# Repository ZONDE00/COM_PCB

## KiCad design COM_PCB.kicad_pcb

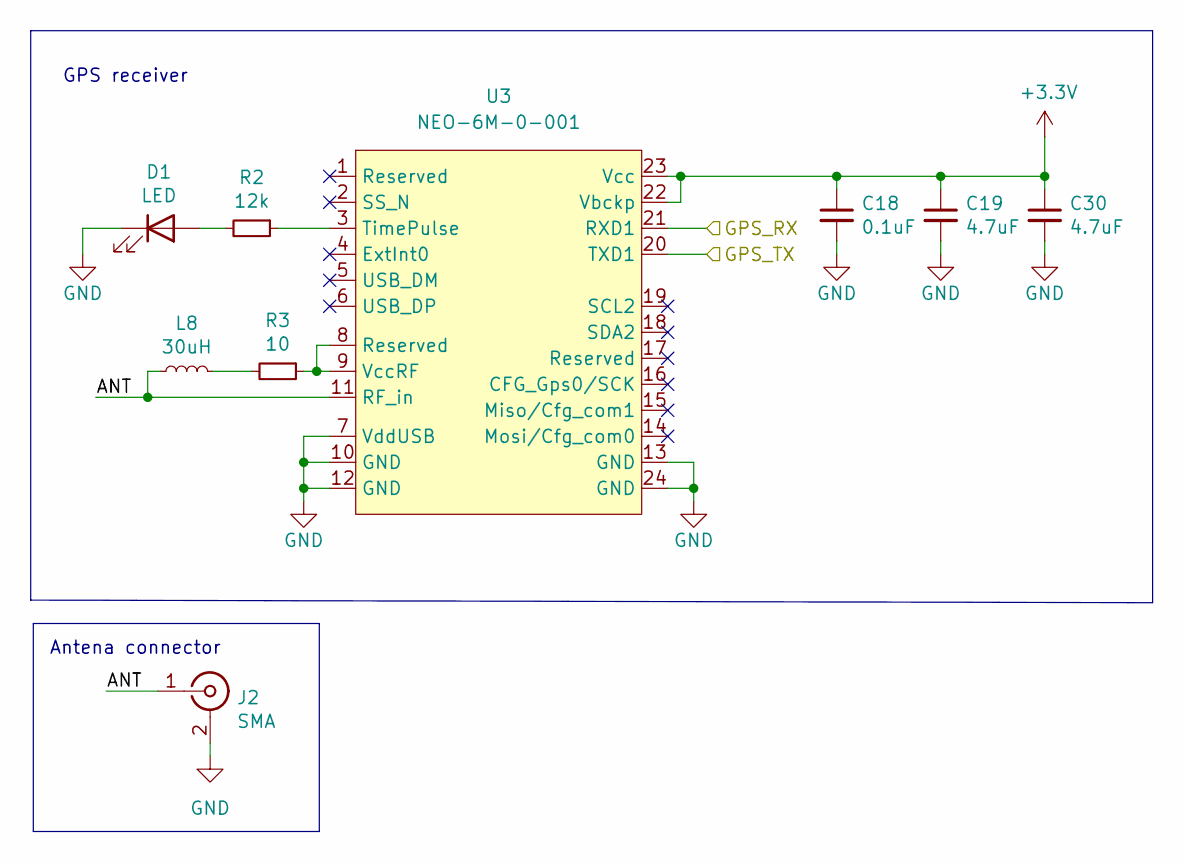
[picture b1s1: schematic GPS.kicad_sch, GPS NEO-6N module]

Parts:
C18: 0.1uF; C_0603_1608Metric
C19, C30: 4.7uF; C_0603_1608Metric
D1: LED; LED_0805_2012Metric_Pad1.15x1.40mm_HandSolder
J2: SMA; SMA_Amphenol_132134-16_Vertical
L8: 30uH; C_0805_2012Metric_Pad1.18x1.45mm_HandSolder
R2: 12k; R_0603_1608Metric_Pad0.98x0.95mm_HandSolder
R3: 10; C_0603_1608Metric
U3: NEO-6M-0-001; XCVR_NEO-6M-GPS

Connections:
+3V3: C18.1, C19.1, C30.1, U3.22 (Vbckp), U3.23 (Vcc); also elsewhere on the board
/GPS/ANT: J2.1 (In), L8.1, U3.11 (RF_in)
/GPS/GPS_RX: U3.21 (RXD1); also elsewhere on the board
/GPS/GPS_TX: U3.20 (TXD1); also elsewhere on the board
GND: C18.2, C19.2, C30.2, D1.1 (K), J2.2 (Ext), U3.7 (VddUSB), U3.10 (GND), U3.12 (GND), U3.13 (GND), U3.24 (GND); also elsewhere on the board
unnamed: D1.2 (A), R2.2
unnamed: L8.2, R3.2
unnamed: R2.1, U3.3 (TimePulse)
unnamed: R3.1, U3.8 (Reserved), U3.9 (VccRF)

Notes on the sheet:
GPS receiver
Antena connector

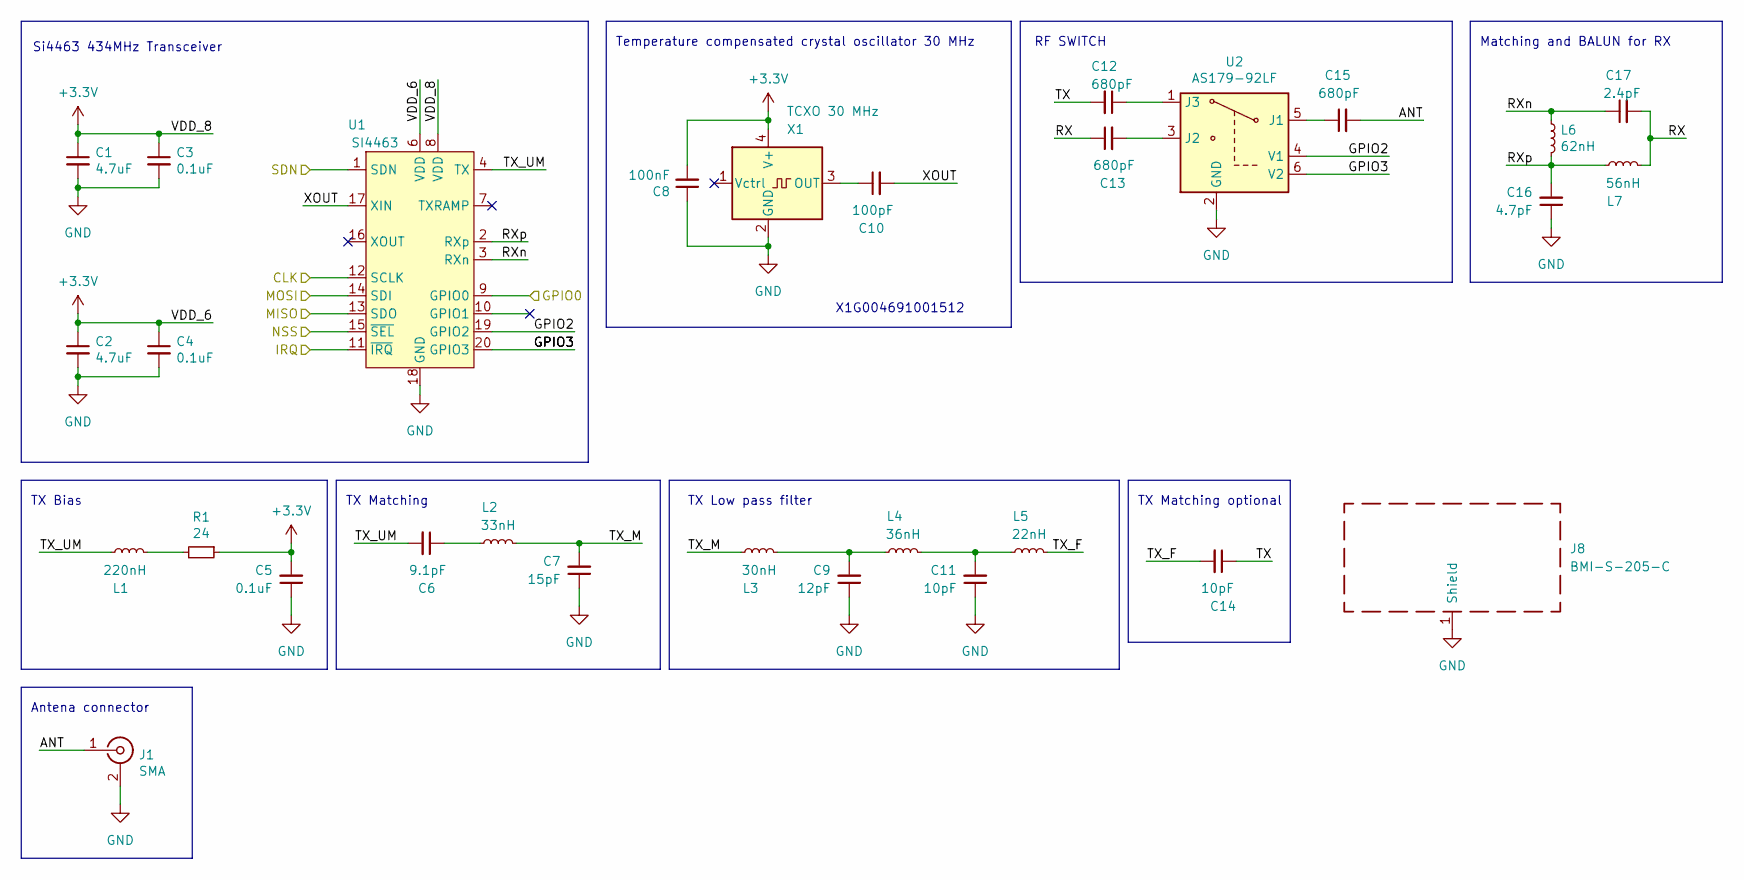
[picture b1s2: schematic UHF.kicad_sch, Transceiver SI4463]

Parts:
C1, C2: 4.7uF; C_0603_1608Metric
C3, C4, C5: 0.1uF; C_0402_1005Metric
C6: 9.1pF; C_0402_1005Metric
C7: 15pF; C_0402_1005Metric
C8: 100nF; C_0402_1005Metric
C9: 12pF; C_0402_1005Metric
C10: 100pF; C_0402_1005Metric
C11, C14: 10pF; C_0402_1005Metric
C12, C13, C15: 680pF; C_0402_1005Metric
C16: 4.7pF; C_0402_1005Metric
C17: 2.4pF; C_0402_1005Metric
J1: SMA; SMA_Amphenol_132134-16_Vertical
J8: BMI-S-205-C; Laird_Technologies_BMI-S-205-F_38.10x25.40mm
L1: 220nH; L_0603_1608Metric
L2: 33nH; L_0402_1005Metric
L3: 30nH; L_0402_1005Metric
L4: 36nH; L_0402_1005Metric
L5: 22nH; L_0402_1005Metric
L6: 62nH; L_0402_1005Metric
L7: 56nH; L_0402_1005Metric
R1: 24; R_0603_1608Metric
U1: SI4463; QFN-20-1EP_4x4mm_P0.5mm_EP2.6x2.6mm_ThermalVias
U2: AS179-92LF; SOT-363_SC-70-6
X1: TCXO 30 MHz; Crystal_SMD_2520-4Pin_2.5x2.0mm

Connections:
+3V3: C1.1, C2.1, C3.1, C4.1, C5.2, C8.2, R1.1, U1.6 (VDD), U1.8 (VDD), X1.4 (V+); also elsewhere on the board
/IO/RF_MISO: U1.13 (SDO); also elsewhere on the board
/IO/RF_MOSI: U1.14 (SDI); also elsewhere on the board
/IO/RF_NSS: U1.15 (~SEL); also elsewhere on the board
/IO/RF_SCK: U1.12 (SCLK); also elsewhere on the board
/MCU/RF_DIO0: U1.9 (GPIO0); also elsewhere on the board
/MCU/RF_IRQ: U1.11 (~IRQ); also elsewhere on the board
/MCU/RF_RST: U1.1 (SDN); also elsewhere on the board
/SI4463/ANT: C15.2, J1.1 (In)
/SI4463/GPIO2: U1.19 (GPIO2), U2.4 (V1)
/SI4463/GPIO3: U1.20 (GPIO3), U2.6 (V2)
/SI4463/RX: C13.1, C17.2, L7.2
/SI4463/RXn: C17.1, L6.1, U1.3 (RXn)
/SI4463/RXp: C16.2, L6.2, L7.1, U1.2 (RXp)
/SI4463/TX: C12.2, C14.1
/SI4463/TX_F: C14.2, L5.2
/SI4463/TX_M: C7.2, L2.2, L3.1
/SI4463/TX_UM: C6.2, L1.1, U1.4 (TX)
/SI4463/XOUT: C10.2, U1.17 (XIN)
GND: C1.2, C2.2, C3.2, C4.2, C5.1, C7.1, C8.1, C9.1, C11.1, C16.1, J1.2 (Ext), J8.1 (Shield), U1.18 (GND), U1.21 (GND), U2.2 (GND), X1.2 (GND); also elsewhere on the board
unnamed: C6.1, L2.1
unnamed: C9.2, L3.2, L4.1
unnamed: C10.1, X1.3 (OUT)
unnamed: C11.2, L4.2, L5.1
unnamed: C12.1, U2.1 (J3)
unnamed: C13.2, U2.3 (J2)
unnamed: C15.1, U2.5 (J1)
unnamed: L1.2, R1.2

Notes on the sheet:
Matching and BALUN for RX
Antena connector
Si4463 434MHz Transceiver
X1G004691001512
RF SWITCH
TX Bias
TX Low pass filter
Temperature compensated crystal oscillator 30 MHz
TX Matching
TX Matching optional

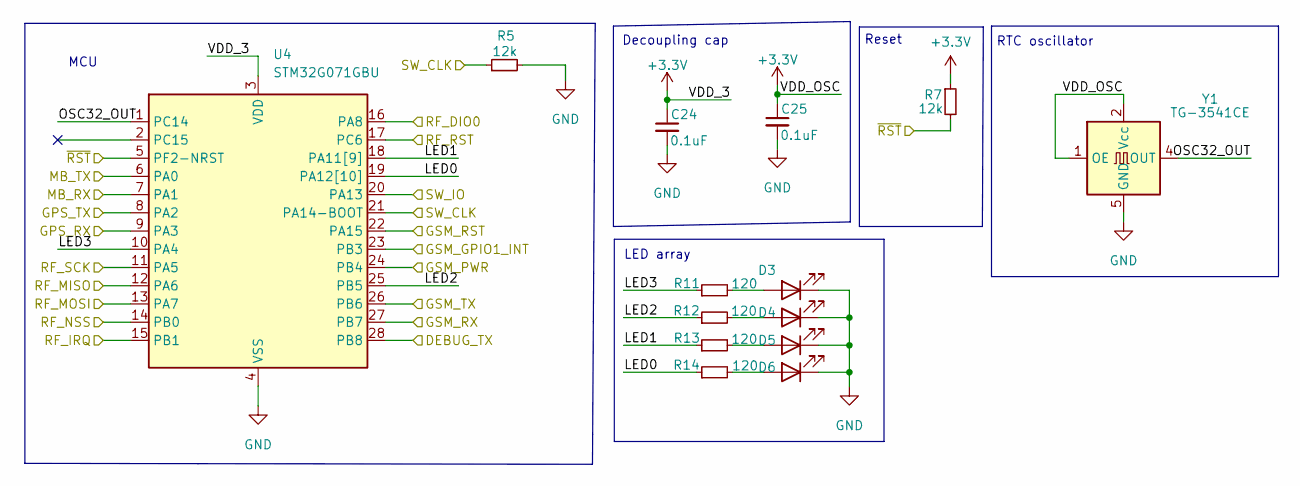
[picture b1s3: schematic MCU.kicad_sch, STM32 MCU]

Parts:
C24, C25: 0.1uF; C_0603_1608Metric
D3, D4, D5, D6: LED; LED_0603_1608Metric
R5: 12k; R_0603_1608Metric
R7: 12k; R_0603_1608Metric_Pad0.98x0.95mm_HandSolder
R11, R12, R13, R14: 120; R_0603_1608Metric
U4: STM32G071GBU; QFN-28_4x4mm_P0.5mm
Y1: TG-3541CE; Oscillator_SMD_SeikoEpson_TG-3541CE_3.2x2.5mm

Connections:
+3V3: C24.1, C25.1, R7.1, U4.3 (VDD), Y1.1 (OE), Y1.2 (Vcc), Y1.3 (Vcc); also elsewhere on the board
/GPRS/GSM_GPIO1_INT: U4.23 (PB3); also elsewhere on the board
/GPRS/GSM_PWR: U4.24 (PB4); also elsewhere on the board
/GPRS/GSM_RST: U4.22 (PA15); also elsewhere on the board
/GPRS/GSM_RX: U4.26 (PB6); also elsewhere on the board
/GPRS/GSM_TX: U4.27 (PB7); also elsewhere on the board
/GPS/GPS_RX: U4.8 (PA2); also elsewhere on the board
/GPS/GPS_TX: U4.9 (PA3); also elsewhere on the board
/IO/MCU_RX: U4.7 (PA1); also elsewhere on the board
/IO/MCU_TX: U4.6 (PA0); also elsewhere on the board
/IO/RF_MISO: U4.12 (PA6); also elsewhere on the board
/IO/RF_MOSI: U4.13 (PA7); also elsewhere on the board
/IO/RF_NSS: U4.14 (PB0); also elsewhere on the board
/IO/RF_SCK: U4.11 (PA5); also elsewhere on the board
/IO/SW_CLK: R5.1, U4.21 (PA14-BOOT); also elsewhere on the board
/IO/SW_IO: U4.20 (PA13); also elsewhere on the board
/IO/TX: U4.28 (PB8); also elsewhere on the board
/IO/~RST: R7.2, U4.5 (PF2-NRST); also elsewhere on the board
/MCU/LED0: R14.1, U4.19 (PA12[10])
/MCU/LED1: R13.1, U4.18 (PA11[9])
/MCU/LED2: R12.1, U4.25 (PB5)
/MCU/LED3: R11.1, U4.10 (PA4)
/MCU/OSC32_OUT: U4.1 (PC14), Y1.4 (OUT)
/MCU/RF_DIO0: U4.16 (PA8); also elsewhere on the board
/MCU/RF_IRQ: U4.15 (PB1); also elsewhere on the board
/MCU/RF_RST: U4.17 (PC6); also elsewhere on the board
GND: C24.2, C25.2, D3.1 (K), D4.1 (K), D5.1 (K), D6.1 (K), R5.2, U4.4 (VSS), Y1.5 (GND), Y1.7 (GND), Y1.8 (GND), Y1.9 (GND); also elsewhere on the board
unnamed: D3.2 (A), R11.2
unnamed: D4.2 (A), R12.2
unnamed: D5.2 (A), R13.2
unnamed: D6.2 (A), R14.2

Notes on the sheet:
Reset
MCU
RTC oscillator
LED array
Decoupling cap

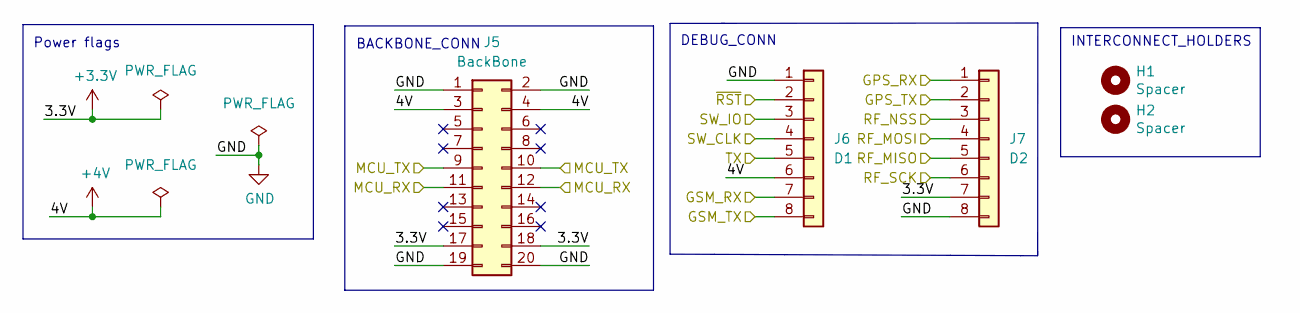
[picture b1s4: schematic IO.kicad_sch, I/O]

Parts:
H1, H2: Spacer; MountingHole_3.2mm_M3
J5: BackBone; PinSocket_2x10_P2.54mm_Horizontal
J6: D1; PinSocket_1x08_P2.54mm_Horizontal
J7: D2; PinSocket_1x08_P2.54mm_Horizontal

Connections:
+3V3: J5.17, J5.18, J7.7; also elsewhere on the board
+4V: J5.3, J5.4, J6.6; also elsewhere on the board
/GPRS/GSM_RX: J6.8; also elsewhere on the board
/GPRS/GSM_TX: J6.7; also elsewhere on the board
/GPS/GPS_RX: J7.1; also elsewhere on the board
/GPS/GPS_TX: J7.2; also elsewhere on the board
/IO/MCU_RX: J5.11, J5.12; also elsewhere on the board
/IO/MCU_TX: J5.9, J5.10; also elsewhere on the board
/IO/RF_MISO: J7.5; also elsewhere on the board
/IO/RF_MOSI: J7.4; also elsewhere on the board
/IO/RF_NSS: J7.3; also elsewhere on the board
/IO/RF_SCK: J7.6; also elsewhere on the board
/IO/SW_CLK: J6.4; also elsewhere on the board
/IO/SW_IO: J6.3; also elsewhere on the board
/IO/TX: J6.5; also elsewhere on the board
/IO/~RST: J6.2; also elsewhere on the board
GND: J5.1, J5.2, J5.19, J5.20, J6.1, J7.8; also elsewhere on the board

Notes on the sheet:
BACKBONE_CONN
DEBUG_CONN
Power flags
INTERCONNECT_HOLDERS

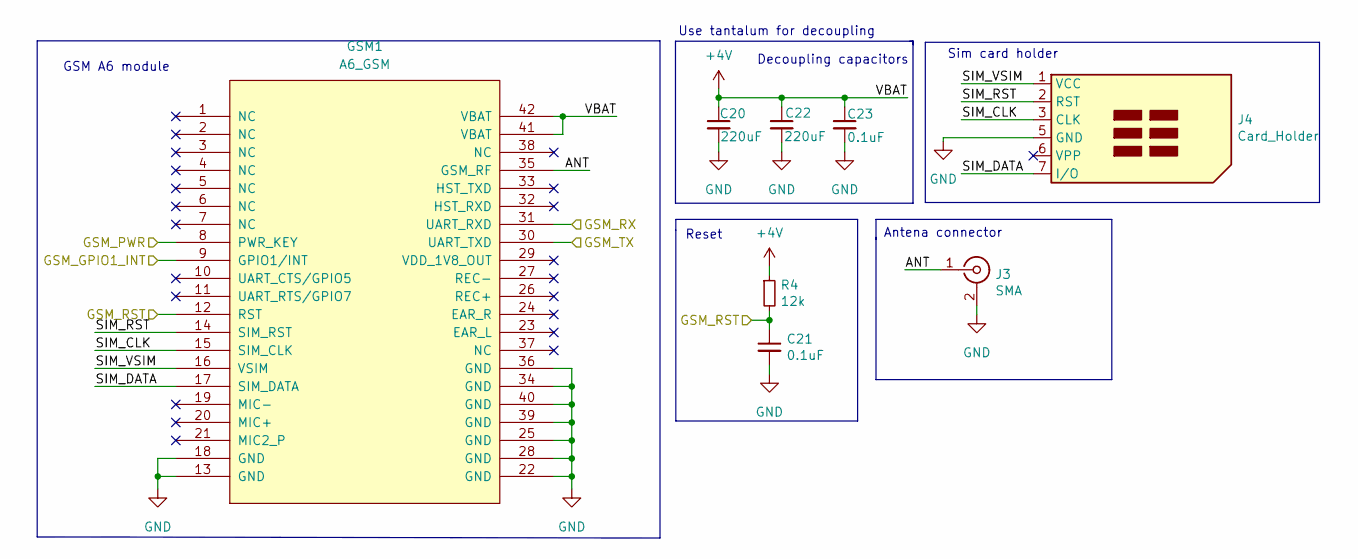
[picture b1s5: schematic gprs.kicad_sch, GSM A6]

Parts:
C20, C22: 220uF; CP_EIA-3528-21_Kemet-B
C21, C23: 0.1uF; C_0603_1608Metric
GSM1: A6_GSM
J3: SMA; SMA_Amphenol_132134-16_Vertical
J4: Card_Holder; MOLEX_78800-0001
R4: 12k; C_0603_1608Metric

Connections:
+4V: C20.1, C22.1, C23.1, GSM1.41 (VBAT), GSM1.42 (VBAT), R4.1; also elsewhere on the board
/GPRS/ANT: GSM1.35 (GSM_RF), J3.1 (In)
/GPRS/GSM_GPIO1_INT: GSM1.9 (GPIO1/INT); also elsewhere on the board
/GPRS/GSM_PWR: GSM1.8 (PWR_KEY); also elsewhere on the board
/GPRS/GSM_RST: C21.1, GSM1.12 (RST), R4.2; also elsewhere on the board
/GPRS/GSM_RX: GSM1.31 (UART_RXD); also elsewhere on the board
/GPRS/GSM_TX: GSM1.30 (UART_TXD); also elsewhere on the board
/GPRS/SIM_CLK: GSM1.15 (SIM_CLK), J4.3 (CLK)
/GPRS/SIM_DATA: GSM1.17 (SIM_DATA), J4.7 (I/O)
/GPRS/SIM_RST: GSM1.14 (SIM_RST), J4.2 (RST)
/GPRS/SIM_VSIM: GSM1.16 (VSIM), J4.1 (VCC)
GND: C20.2, C21.2, C22.2, C23.2, GSM1.13 (GND), GSM1.18 (GND), GSM1.22 (GND), GSM1.25 (GND), GSM1.28 (GND), GSM1.34 (GND), GSM1.36 (GND), GSM1.39 (GND), GSM1.40 (GND), J3.2 (Ext), J4.5 (GND); also elsewhere on the board

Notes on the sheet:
Use tantalum for decoupling
Decoupling capacitors
Reset
GSM A6 module
Sim card holder
Antena connector

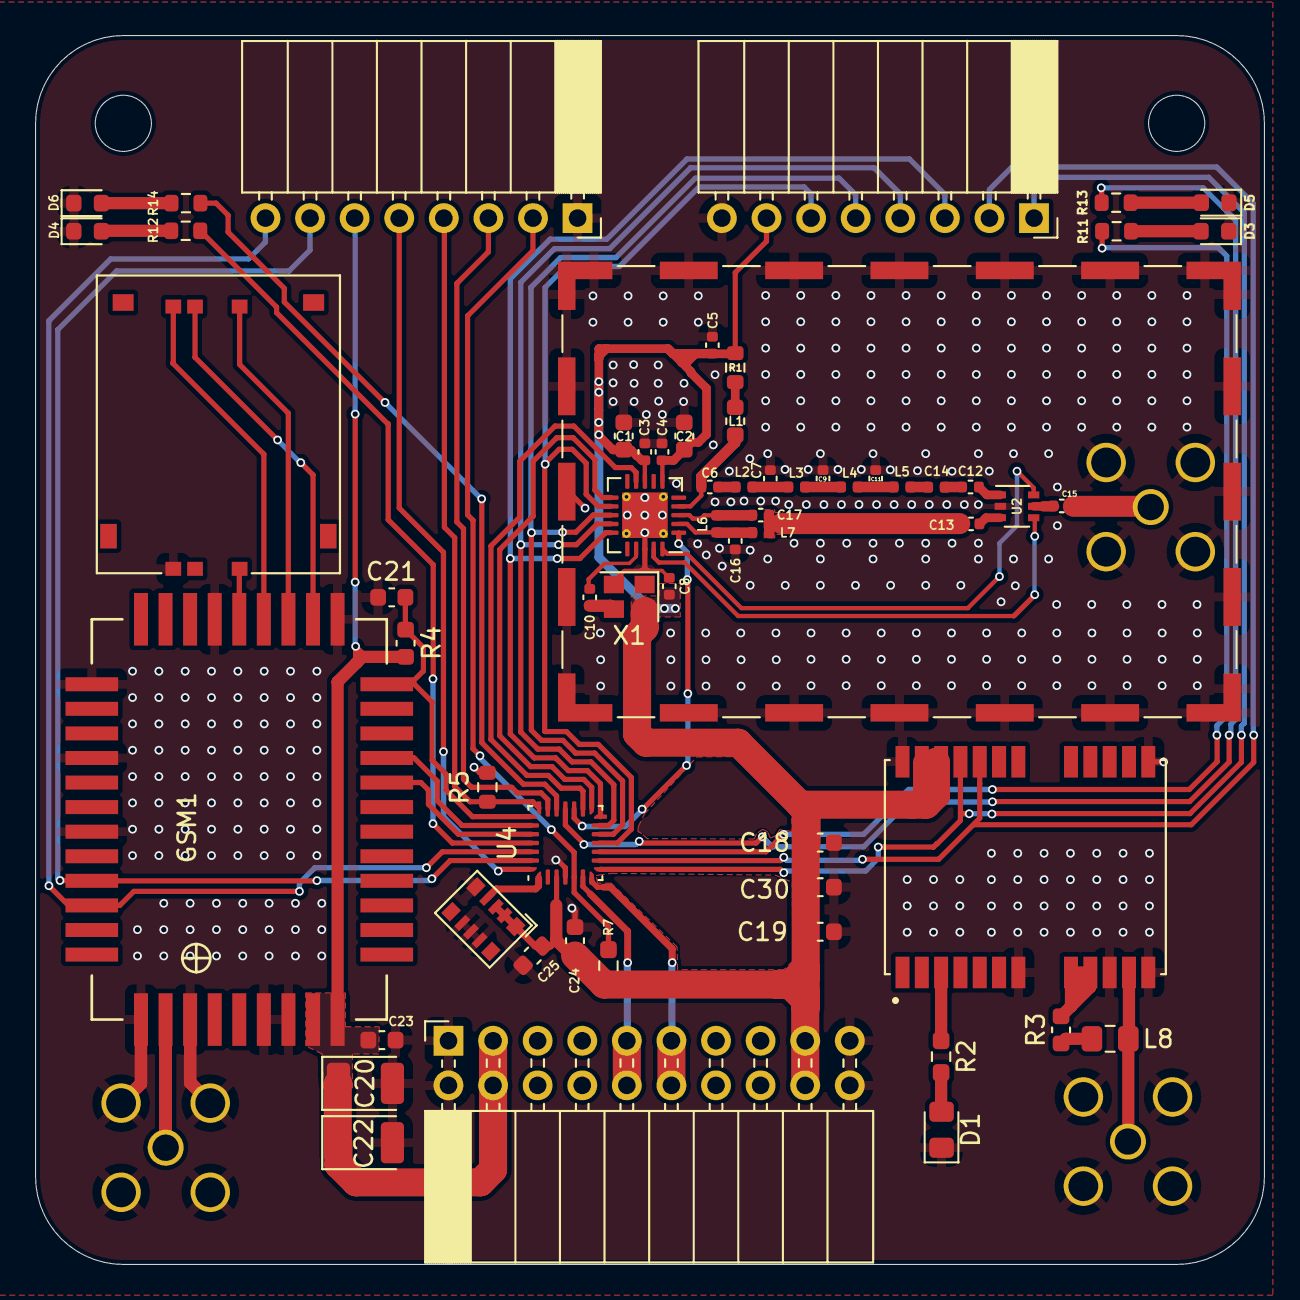
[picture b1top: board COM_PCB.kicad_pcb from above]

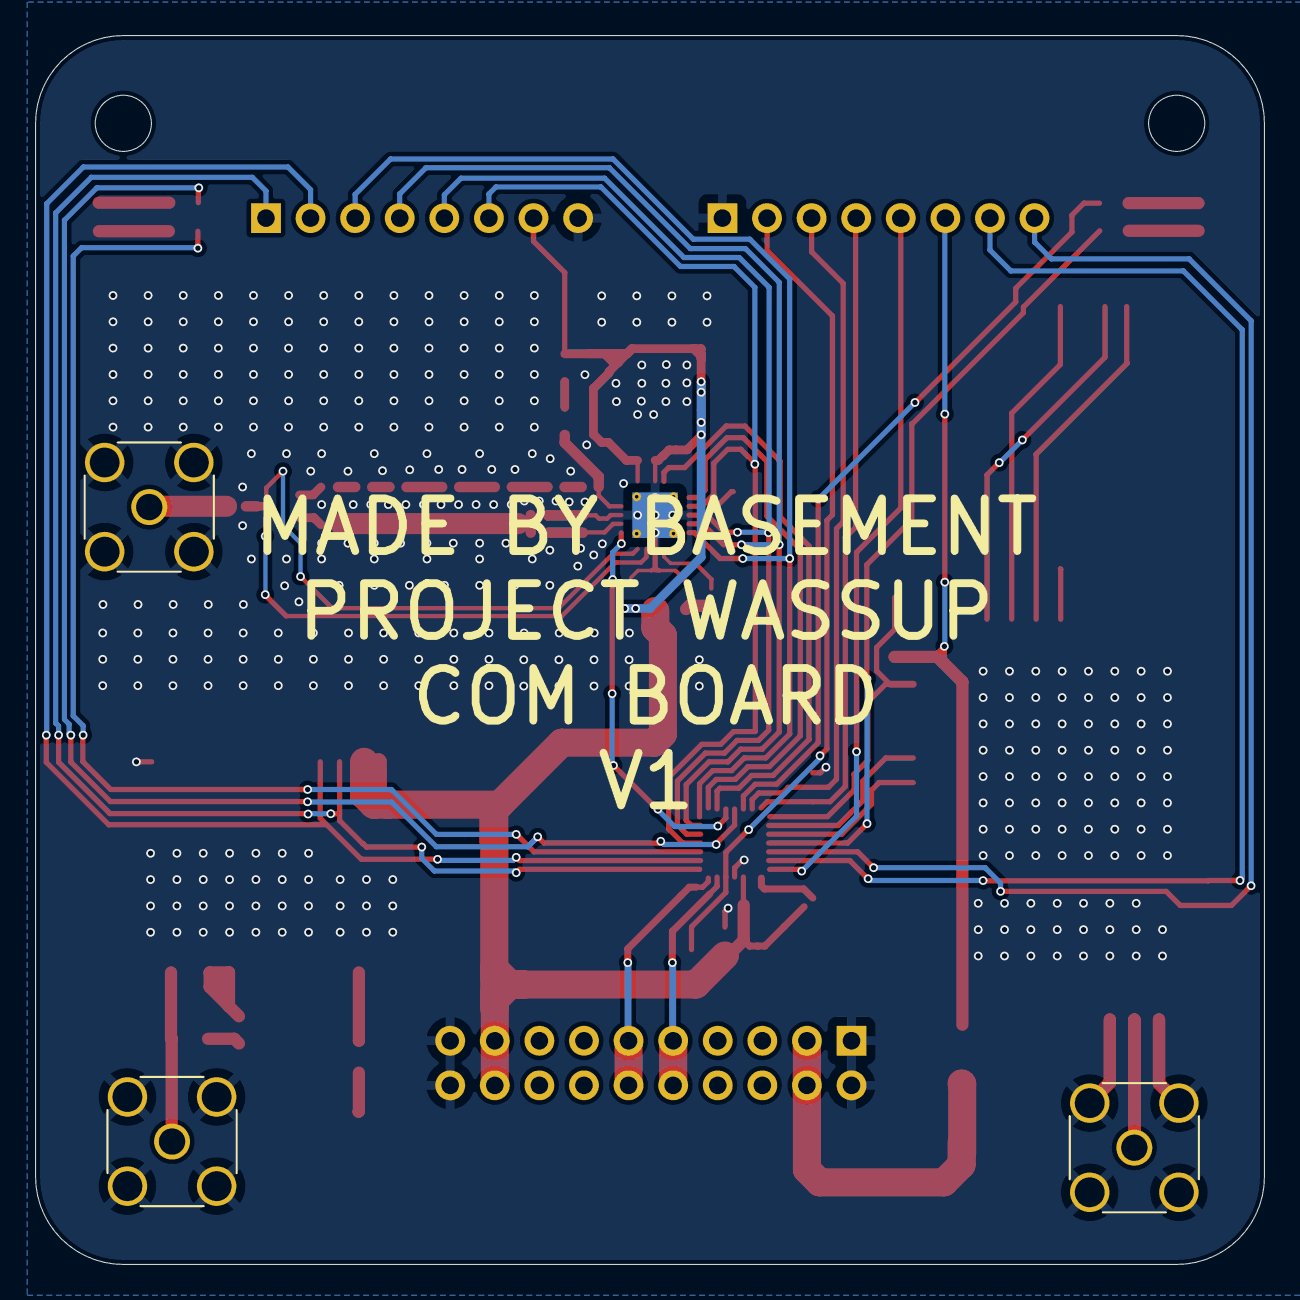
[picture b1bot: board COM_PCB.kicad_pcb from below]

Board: 2 copper layers, 70.0 x 70.0 mm, 66 parts (3 on the bottom side), 61 nets.

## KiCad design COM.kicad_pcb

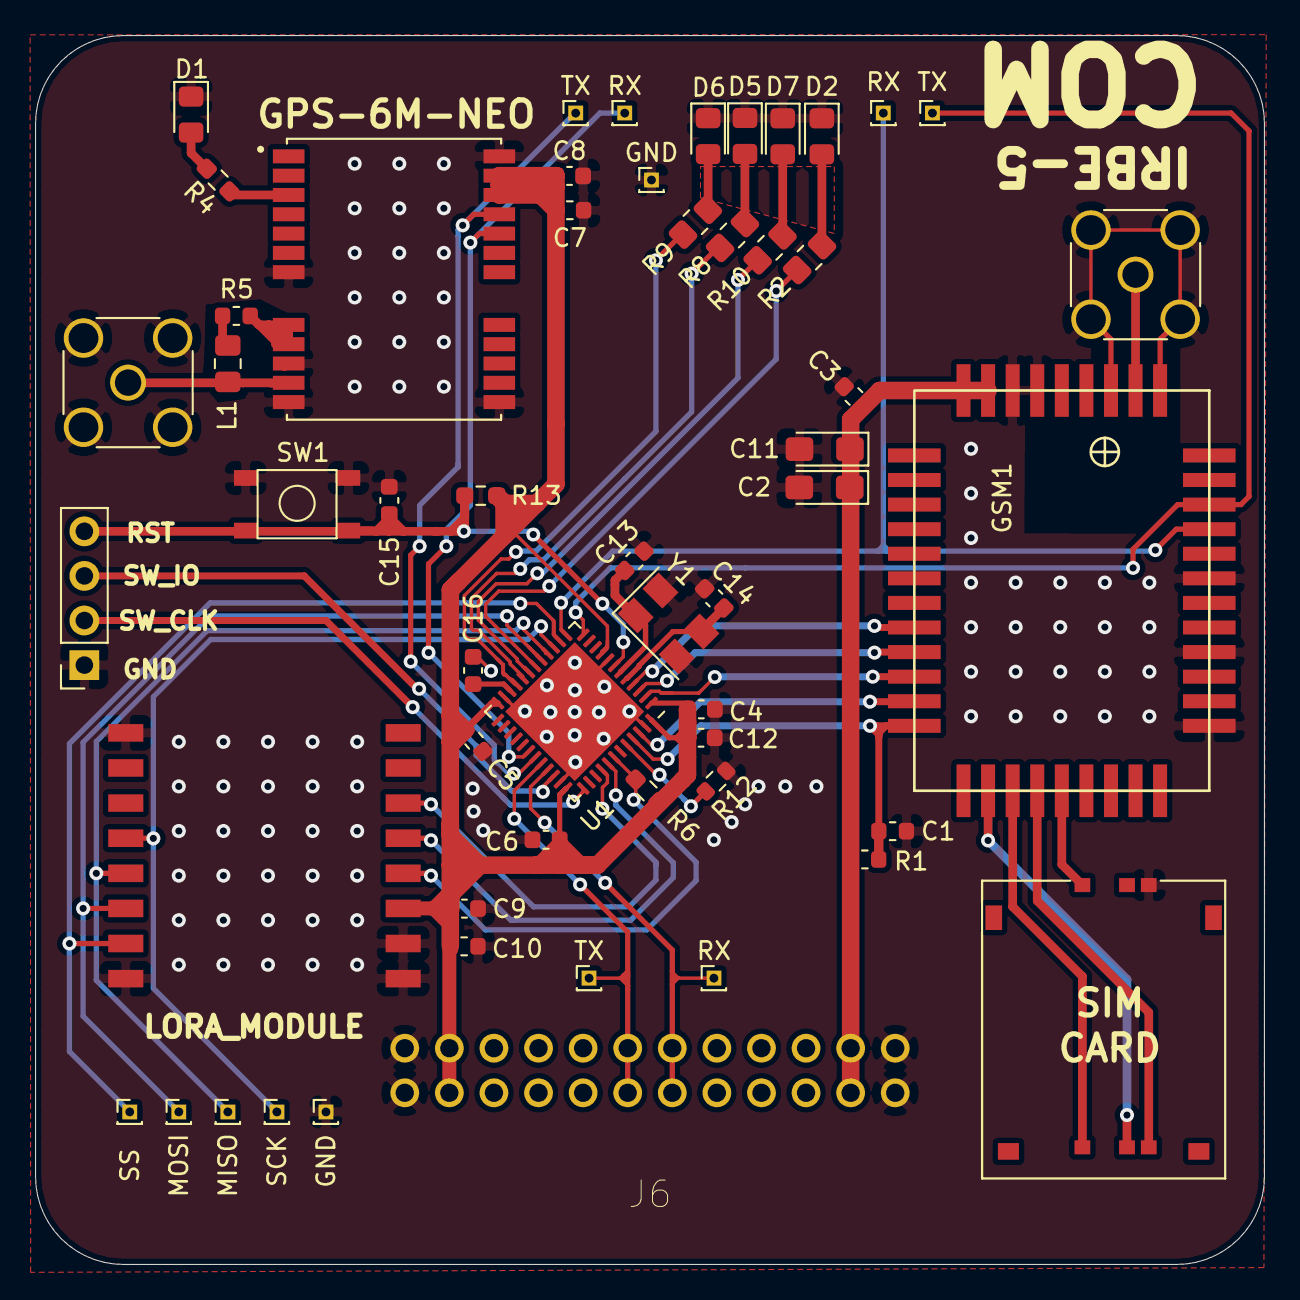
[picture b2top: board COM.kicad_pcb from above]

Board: 2 copper layers, 70.0 x 70.0 mm, 55 parts (0 on the bottom side), 46 nets.

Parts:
C1, C3, C4, C5, C6, C7, C10, C12: 0.1uF; C_0603_1608Metric
C2, C11: 220uF; CP_EIA-3216-10_Kemet-I_Pad1.58x1.35mm_HandSolder
C8, C9: 10uF; C_0603_1608Metric
C13, C14: 22pF; C_0603_1608Metric
C15: 220nF; C_0603_1608Metric
C16: 4.7uF; C_0603_1608Metric
D1: LED; LED_0805_2012Metric_Pad1.15x1.40mm_HandSolder
D2, D5, D6, D7: BLUE; LED_0805_2012Metric_Pad1.15x1.40mm_HandSolder
GND: TestPoint; PinHeader_1x01_P1.00mm_Vertical
GND#2: TestPoint; PinHeader_1x01_P1.00mm_Vertical
GSM1: A6_GSM
J1, J4: Conn_Coaxial; SMA_Amphenol_132134-16_Vertical
J2: SIM_Card; MOLEX_78800-0001
J3: ST_LINK; PinSocket_1x04_P2.54mm_Vertical
J6: 02x12; SAMTEC-SSW-112-02-X-D-RA
L1: 27uH; C_0805_2012Metric_Pad1.18x1.45mm_HandSolder
MISO: TestPoint; PinHeader_1x01_P1.00mm_Vertical
MOSI: TestPoint; PinHeader_1x01_P1.00mm_Vertical
R1: 10k; C_0603_1608Metric
R2, R8, R9, R10: 75; R_0805_2012Metric_Pad1.20x1.40mm_HandSolder
R4: 1k; R_0603_1608Metric_Pad0.98x0.95mm_HandSolder
R5: 10; C_0603_1608Metric
R6: 10k; R_0603_1608Metric_Pad0.98x0.95mm_HandSolder
R12: 12k; R_0603_1608Metric
R13: 12k; R_0603_1608Metric_Pad0.98x0.95mm_HandSolder
RX: TestPoint; PinHeader_1x01_P1.00mm_Vertical
RX#2, RX#3: TestPoint; PinHeader_1x01_P1.00mm_Vertical
SCK: TestPoint; PinHeader_1x01_P1.00mm_Vertical
SS: TestPoint; PinHeader_1x01_P1.00mm_Vertical
SW1: Reset; little_button
TX: TestPoint; PinHeader_1x01_P1.00mm_Vertical
TX#2, TX#3: TestPoint; PinHeader_1x01_P1.00mm_Vertical
U1: STM32F401CEUx; QFN-48-1EP_7x7mm_P0.5mm_EP5.6x5.6mm
U2: NEO-6M-0-001; XCVR_NEO-6M-GPS
U3: Ai-Thinker_Ra-02
Y1: MCSJK; Crystal_SMD_5032-4Pin_5.0x3.2mm

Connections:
3.3V: C4.1, C5.1, C6.1, C7.1, C8.1, C9.1, C10.1, C12.1, J6.11, J6.14, R6.2, R13.1, U1.1, U1.9, U1.24, U1.36, U1.48, U2.22, U2.23, U3.3
4V: C2.1, C3.1, C11.1, GSM1.41, GSM1.42, J6.2, J6.23, R1.1
/GPS/ANT: J4.1, L1.1, U2.11
/MCU/SW_CLK: J3.2, U1.37
/MCU/SW_IO: J3.3, U1.34
/MCU/~RST: C15.1, J3.4, R13.2, SW1.1, U1.7
/gprs/ANT: GSM1.35, J1.1
/gprs/SIM_CLK: GSM1.15, J2.3
/gprs/SIM_DATA: GSM1.17, J2.7
/gprs/SIM_RST: GSM1.14, J2.2
/gprs/SIM_VSIM: GSM1.16, J2.1
GND: C1.2, C2.2, C3.2, C4.2, C5.2, C6.2, C7.2, C8.2, C9.2, C10.2, C11.2, C12.2, C13.2, C14.2, C15.2, C16.2, D1.1, D2.1, D5.1, D6.1, D7.1, GND.1, GND#2.1, GSM1.22, GSM1.25, GSM1.28, GSM1.34, GSM1.36, GSM1.39, GSM1.40, J1.2, J2.5, J3.1, J4.2, J6.1, J6.12, J6.13, J6.24, R12.2, SW1.2, U1.8, U1.23, U1.35, U1.47, U1.49, U2.7, U2.10, U2.12, U2.13, U2.24, U3.1, U3.2, U3.9, U3.16, Y1.2, Y1.4
GPS_RX: RX#2.1, U1.30, U2.20
GPS_TX: TX#3.1, U1.31, U2.21
GSM_CTS: GSM1.10, U1.2
GSM_GPIO1INT: GSM1.9, U1.3
GSM_PWR: GSM1.8, U1.4
GSM_RST: C1.1, GSM1.12, R1.2, U1.45
GSM_RTS: GSM1.11, U1.46
GSM_RX: GSM1.30, RX#3.1, U1.13
GSM_TX: GSM1.31, TX#2.1, U1.12
unnamed: C13.1, U1.6, Y1.1
unnamed: C14.1, U1.5, Y1.3
unnamed: C16.1, U1.22
unnamed: D1.2, R4.2
unnamed: D2.2, R2.2
unnamed: D5.2, R8.2
unnamed: D6.2, R9.2
unnamed: D7.2, R10.2
unnamed: L1.2, R5.2
unnamed: R2.1, U1.18
unnamed: R4.1, U2.3
unnamed: R5.1, U2.8, U2.9
unnamed: R8.1, U1.20
unnamed: R9.1, U1.21
unnamed: R10.1, U1.19
unnamed: R12.1, U1.44
RF_DIO0: U1.41, U3.5
RF_DIO1: U1.40, U3.6
RF_MISO: MISO.1, U1.16, U3.13
RF_MOSI: MOSI.1, U1.17, U3.14
RF_NSS: SS.1, U1.14, U3.15
RF_RST: R6.1, U1.42, U3.4
RF_SCK: SCK.1, U1.15, U3.12
RX: J6.6, J6.19, RX.1, U1.33
TX: J6.7, J6.18, TX.1, U1.32

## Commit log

2022-07-31 KiCad unfinished 0.1
    Unfinished KiCad project.
    Schematic part is almost done, need to add DEBUG interface (connect all necessary pins to DEBUG interface).
    Need to update PCB.
2022-08-01 KiCad 0.2v
    Schematics done.
    Have to assign footprints to corresponding components.
    Completely rework PCB.
2022-08-02 KiCad 0.3v
    Improved aesthetics.
2022-09-18 0.1v COM_PCB KiCad
    First iteration of COM PCB.
2022-09-25 solved issues
    Crystal changes and some routing.
